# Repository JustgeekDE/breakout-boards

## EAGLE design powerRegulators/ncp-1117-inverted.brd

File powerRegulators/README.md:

# Power Regulators
Adapters to use the LM1117 SMD adjustable regulators on a breadboard.

The normal version has the same pinout as the common L78xx regulators, when looking at the components. The Inverted version has the L78xx footprint, when looking at the silkscreen side.

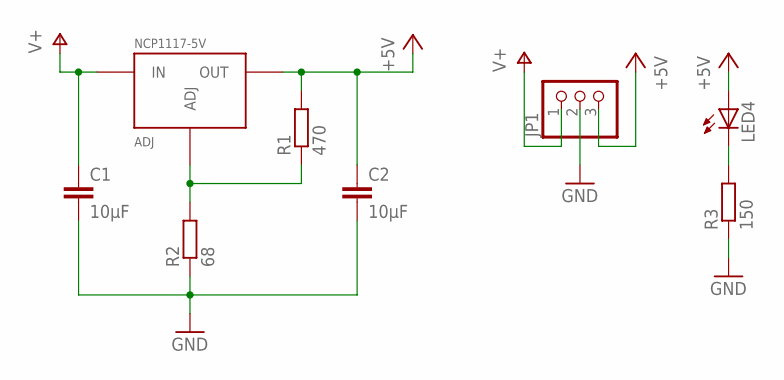
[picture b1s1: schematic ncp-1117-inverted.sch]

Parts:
C1, C2: 10µF; C0805
JP1: PINHD-1X3; 1X03
LED4: LEDCHIP-LED0603; CHIP-LED0603
NCP1117-5V: ADJ; TO252
R1: 470; R0603
R2: 68; R0603
R3: 150; R0603

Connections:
+5V: C2.1, JP1.3, LED4.A, NCP1117-5V.3 (OUT), R1.2
GND: C1.2, C2.2, JP1.2, R2.1, R3.1
unnamed: LED4.C, R3.2
unnamed: NCP1117-5V.1 (ADJ), R1.1, R2.2
V+: C1.1, JP1.1, NCP1117-5V.2 (IN)

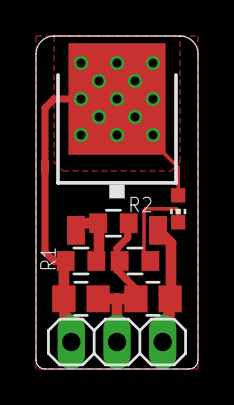
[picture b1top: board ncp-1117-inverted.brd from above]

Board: 2 copper layers, 9.0 x 18.5 mm, 9 parts (1 on the bottom side), 5 nets.

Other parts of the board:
U$1: LOGO-JUSTGEEK-XS

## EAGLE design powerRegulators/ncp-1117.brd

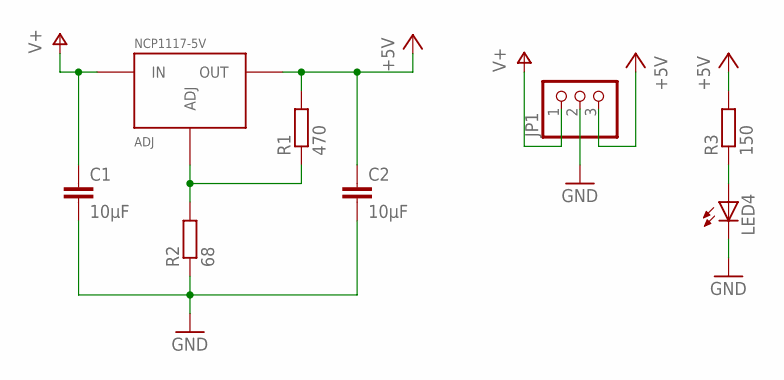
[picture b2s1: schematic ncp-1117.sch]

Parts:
C1, C2: 10µF; C0805
JP1: PINHD-1X3; 1X03
LED4: LEDCHIP-LED0603; CHIP-LED0603
NCP1117-5V: ADJ; TO252
R1: 470; R0603
R2: 68; R0603
R3: 150; R0603

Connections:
+5V: C2.1, JP1.3, NCP1117-5V.3 (OUT), R1.2, R3.2
GND: C1.2, C2.2, JP1.2, LED4.C, R2.1
unnamed: LED4.A, R3.1
unnamed: NCP1117-5V.1 (ADJ), R1.1, R2.2
V+: C1.1, JP1.1, NCP1117-5V.2 (IN)

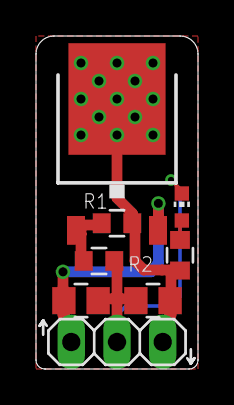
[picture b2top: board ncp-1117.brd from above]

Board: 2 copper layers, 9.0 x 18.5 mm, 9 parts (1 on the bottom side), 5 nets.

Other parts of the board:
U$1: LOGO-JUSTGEEK-XS

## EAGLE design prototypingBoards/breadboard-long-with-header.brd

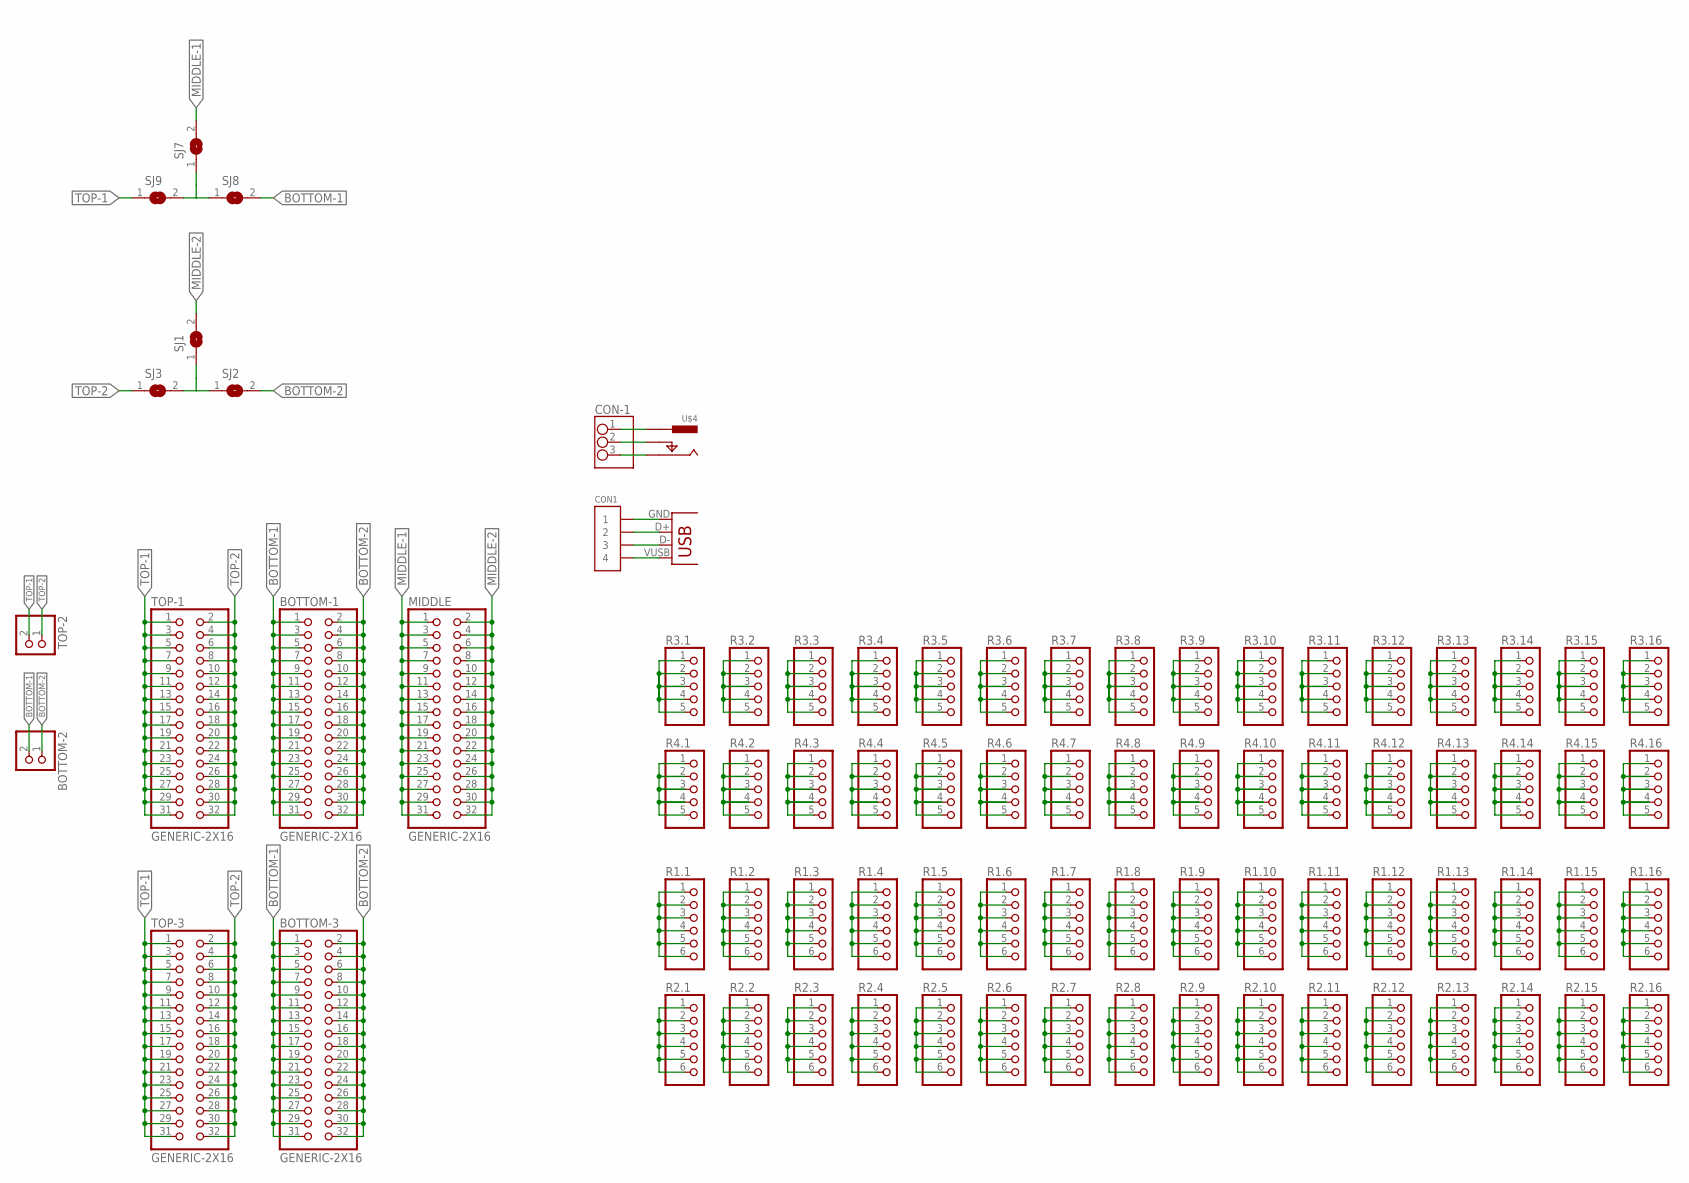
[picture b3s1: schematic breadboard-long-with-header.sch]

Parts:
BOTTOM-1, BOTTOM-3: GENERIC-2X16; PINHEADER-100MIL-2X16-NOSILK
BOTTOM-2: GENERIC-1X2; PINHEADER-100MIL-1X2-NOSILK
CON1: GENERIC-1X4STRAIGHT; PINHEADER-100MIL-1X4-NOSILK
CON-1: GENERIC-1X3; PINHEADER-100MIL-1X3-NOSILK
MIDDLE: GENERIC-2X16; PINHEADER-100MIL-2X16-NOSILK
R1.1, R1.2, R1.3, R1.4, R1.5, R1.6, R1.7, R1.8, R1.9, R1.10, R1.11, R1.12, R1.13, R1.14, R1.15, R1.16, R2.1, R2.2, R2.3, R2.4, R2.5, R2.6, R2.7, R2.8, R2.9, R2.10, R2.11, R2.12, R2.13, R2.14, R2.15, R2.16: GENERIC-1X6; PINHEADER-100MIL-1X6-NOSILK
R3.1, R3.2, R3.3, R3.4, R3.5, R3.6, R3.7, R3.8, R3.9, R3.10, R3.11, R3.12, R3.13, R3.14, R3.15, R3.16, R4.1, R4.2, R4.3, R4.4, R4.5, R4.6, R4.7, R4.8, R4.9, R4.10, R4.11, R4.12, R4.13, R4.14, R4.15, R4.16: GENERIC-1X5; PINHEADER-100MIL-1X5-NOSILK
SJ1, SJ2, SJ3, SJ7, SJ8, SJ9: SJ
TOP-1, TOP-3: GENERIC-2X16; PINHEADER-100MIL-2X16-NOSILK
TOP-2: GENERIC-1X2; PINHEADER-100MIL-1X2-NOSILK
U$3: USBMINI-HAND; USB-MINI-B-HAND_EXTRA_LONG
U$4: POWER-BARREL_JACKEBAY; POWER-BARREL-2MM1-EBAY

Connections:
BOTTOM-1: BOTTOM-1.1, BOTTOM-1.3, BOTTOM-1.5, BOTTOM-1.7, BOTTOM-1.9, BOTTOM-1.11, BOTTOM-1.13, BOTTOM-1.15, BOTTOM-1.17, BOTTOM-1.19, BOTTOM-1.21, BOTTOM-1.23, BOTTOM-1.25, BOTTOM-1.27, BOTTOM-1.29, BOTTOM-1.31, BOTTOM-2.2, BOTTOM-3.1, BOTTOM-3.3, BOTTOM-3.5, BOTTOM-3.7, BOTTOM-3.9, BOTTOM-3.11, BOTTOM-3.13, BOTTOM-3.15, BOTTOM-3.17, BOTTOM-3.19, BOTTOM-3.21, BOTTOM-3.23, BOTTOM-3.25, BOTTOM-3.27, BOTTOM-3.29, BOTTOM-3.31, SJ8.2
BOTTOM-2: BOTTOM-1.2, BOTTOM-1.4, BOTTOM-1.6, BOTTOM-1.8, BOTTOM-1.10, BOTTOM-1.12, BOTTOM-1.14, BOTTOM-1.16, BOTTOM-1.18, BOTTOM-1.20, BOTTOM-1.22, BOTTOM-1.24, BOTTOM-1.26, BOTTOM-1.28, BOTTOM-1.30, BOTTOM-1.32, BOTTOM-2.1, BOTTOM-3.2, BOTTOM-3.4, BOTTOM-3.6, BOTTOM-3.8, BOTTOM-3.10, BOTTOM-3.12, BOTTOM-3.14, BOTTOM-3.16, BOTTOM-3.18, BOTTOM-3.20, BOTTOM-3.22, BOTTOM-3.24, BOTTOM-3.26, BOTTOM-3.28, BOTTOM-3.30, BOTTOM-3.32, SJ2.2
CENTER: CON-1.1, U$4.P$4 (CENTER)
MIDDLE-1: MIDDLE.1, MIDDLE.3, MIDDLE.5, MIDDLE.7, MIDDLE.9, MIDDLE.11, MIDDLE.13, MIDDLE.15, MIDDLE.17, MIDDLE.19, MIDDLE.21, MIDDLE.23, MIDDLE.25, MIDDLE.27, MIDDLE.29, MIDDLE.31, SJ7.2
MIDDLE-2: MIDDLE.2, MIDDLE.4, MIDDLE.6, MIDDLE.8, MIDDLE.10, MIDDLE.12, MIDDLE.14, MIDDLE.16, MIDDLE.18, MIDDLE.20, MIDDLE.22, MIDDLE.24, MIDDLE.26, MIDDLE.28, MIDDLE.30, MIDDLE.32, SJ1.2
unnamed: R3.1.1, R3.1.2, R3.1.3, R3.1.4, R3.1.5
unnamed: R4.1.1, R4.1.2, R4.1.3, R4.1.4, R4.1.5
unnamed: R2.6.1, R2.6.2, R2.6.3, R2.6.4, R2.6.5, R2.6.6
unnamed: R1.6.1, R1.6.2, R1.6.3, R1.6.4, R1.6.5, R1.6.6
unnamed: R2.7.1, R2.7.2, R2.7.3, R2.7.4, R2.7.5, R2.7.6
unnamed: R1.7.1, R1.7.2, R1.7.3, R1.7.4, R1.7.5, R1.7.6
unnamed: R2.8.1, R2.8.2, R2.8.3, R2.8.4, R2.8.5, R2.8.6
unnamed: R1.8.1, R1.8.2, R1.8.3, R1.8.4, R1.8.5, R1.8.6
unnamed: R2.9.1, R2.9.2, R2.9.3, R2.9.4, R2.9.5, R2.9.6
unnamed: R2.1.1, R2.1.2, R2.1.3, R2.1.4, R2.1.5, R2.1.6
unnamed: R1.1.1, R1.1.2, R1.1.3, R1.1.4, R1.1.5, R1.1.6
unnamed: R2.3.1, R2.3.2, R2.3.3, R2.3.4, R2.3.5, R2.3.6
unnamed: R2.2.1, R2.2.2, R2.2.3, R2.2.4, R2.2.5, R2.2.6
unnamed: R1.2.1, R1.2.2, R1.2.3, R1.2.4, R1.2.5, R1.2.6
unnamed: R1.3.1, R1.3.2, R1.3.3, R1.3.4, R1.3.5, R1.3.6
unnamed: R2.4.1, R2.4.2, R2.4.3, R2.4.4, R2.4.5, R2.4.6
unnamed: R1.4.1, R1.4.2, R1.4.3, R1.4.4, R1.4.5, R1.4.6
unnamed: R2.5.1, R2.5.2, R2.5.3, R2.5.4, R2.5.5, R2.5.6
unnamed: R1.5.1, R1.5.2, R1.5.3, R1.5.4, R1.5.5, R1.5.6
unnamed: R3.2.1, R3.2.2, R3.2.3, R3.2.4, R3.2.5
unnamed: R4.2.1, R4.2.2, R4.2.3, R4.2.4, R4.2.5
unnamed: R3.3.1, R3.3.2, R3.3.3, R3.3.4, R3.3.5
unnamed: R4.3.1, R4.3.2, R4.3.3, R4.3.4, R4.3.5
unnamed: R3.4.1, R3.4.2, R3.4.3, R3.4.4, R3.4.5
unnamed: R4.4.1, R4.4.2, R4.4.3, R4.4.4, R4.4.5
unnamed: R3.5.1, R3.5.2, R3.5.3, R3.5.4, R3.5.5
unnamed: R4.5.1, R4.5.2, R4.5.3, R4.5.4, R4.5.5
unnamed: R3.6.1, R3.6.2, R3.6.3, R3.6.4, R3.6.5
unnamed: R4.6.1, R4.6.2, R4.6.3, R4.6.4, R4.6.5
unnamed: R3.7.1, R3.7.2, R3.7.3, R3.7.4, R3.7.5
unnamed: R4.7.1, R4.7.2, R4.7.3, R4.7.4, R4.7.5
unnamed: R3.8.1, R3.8.2, R3.8.3, R3.8.4, R3.8.5
unnamed: R4.8.1, R4.8.2, R4.8.3, R4.8.4, R4.8.5
unnamed: R3.9.1, R3.9.2, R3.9.3, R3.9.4, R3.9.5
unnamed: R4.9.1, R4.9.2, R4.9.3, R4.9.4, R4.9.5
unnamed: SJ1.1, SJ2.1, SJ3.2
unnamed: R1.9.1, R1.9.2, R1.9.3, R1.9.4, R1.9.5, R1.9.6
unnamed: SJ7.1, SJ8.1, SJ9.2
unnamed: R2.10.1, R2.10.2, R2.10.3, R2.10.4, R2.10.5, R2.10.6
unnamed: R1.10.1, R1.10.2, R1.10.3, R1.10.4, R1.10.5, R1.10.6
unnamed: R2.11.1, R2.11.2, R2.11.3, R2.11.4, R2.11.5, R2.11.6
unnamed: R1.11.1, R1.11.2, R1.11.3, R1.11.4, R1.11.5, R1.11.6
unnamed: R2.12.1, R2.12.2, R2.12.3, R2.12.4, R2.12.5, R2.12.6
unnamed: R1.12.1, R1.12.2, R1.12.3, R1.12.4, R1.12.5, R1.12.6
unnamed: R2.13.1, R2.13.2, R2.13.3, R2.13.4, R2.13.5, R2.13.6
unnamed: R1.13.1, R1.13.2, R1.13.3, R1.13.4, R1.13.5, R1.13.6
unnamed: R2.14.1, R2.14.2, R2.14.3, R2.14.4, R2.14.5, R2.14.6
unnamed: R1.14.1, R1.14.2, R1.14.3, R1.14.4, R1.14.5, R1.14.6
unnamed: R2.15.1, R2.15.2, R2.15.3, R2.15.4, R2.15.5, R2.15.6
unnamed: R1.15.1, R1.15.2, R1.15.3, R1.15.4, R1.15.5, R1.15.6
unnamed: R2.16.1, R2.16.2, R2.16.3, R2.16.4, R2.16.5, R2.16.6
unnamed: R1.16.1, R1.16.2, R1.16.3, R1.16.4, R1.16.5, R1.16.6
unnamed: R3.10.1, R3.10.2, R3.10.3, R3.10.4, R3.10.5
unnamed: R4.10.1, R4.10.2, R4.10.3, R4.10.4, R4.10.5
unnamed: R3.11.1, R3.11.2, R3.11.3, R3.11.4, R3.11.5
unnamed: R4.11.1, R4.11.2, R4.11.3, R4.11.4, R4.11.5
unnamed: R3.12.1, R3.12.2, R3.12.3, R3.12.4, R3.12.5
unnamed: R4.12.1, R4.12.2, R4.12.3, R4.12.4, R4.12.5
unnamed: R3.13.1, R3.13.2, R3.13.3, R3.13.4, R3.13.5
unnamed: R4.13.1, R4.13.2, R4.13.3, R4.13.4, R4.13.5
unnamed: R3.14.1, R3.14.2, R3.14.3, R3.14.4, R3.14.5
unnamed: R4.14.1, R4.14.2, R4.14.3, R4.14.4, R4.14.5
unnamed: R3.15.1, R3.15.2, R3.15.3, R3.15.4, R3.15.5
unnamed: R4.15.1, R4.15.2, R4.15.3, R4.15.4, R4.15.5
unnamed: R3.16.1, R3.16.2, R3.16.3, R3.16.4, R3.16.5
unnamed: R4.16.1, R4.16.2, R4.16.3, R4.16.4, R4.16.5
SLEEVE: CON-1.3, U$4.P$3 (OUTER)
SWITCH: CON-1.2, U$4.P$2 (SWITCH)
TOP-1: SJ9.1, TOP-1.1, TOP-1.3, TOP-1.5, TOP-1.7, TOP-1.9, TOP-1.11, TOP-1.13, TOP-1.15, TOP-1.17, TOP-1.19, TOP-1.21, TOP-1.23, TOP-1.25, TOP-1.27, TOP-1.29, TOP-1.31, TOP-2.2, TOP-3.1, TOP-3.3, TOP-3.5, TOP-3.7, TOP-3.9, TOP-3.11, TOP-3.13, TOP-3.15, TOP-3.17, TOP-3.19, TOP-3.21, TOP-3.23, TOP-3.25, TOP-3.27, TOP-3.29, TOP-3.31
TOP-2: SJ3.1, TOP-1.2, TOP-1.4, TOP-1.6, TOP-1.8, TOP-1.10, TOP-1.12, TOP-1.14, TOP-1.16, TOP-1.18, TOP-1.20, TOP-1.22, TOP-1.24, TOP-1.26, TOP-1.28, TOP-1.30, TOP-1.32, TOP-2.1, TOP-3.2, TOP-3.4, TOP-3.6, TOP-3.8, TOP-3.10, TOP-3.12, TOP-3.14, TOP-3.16, TOP-3.18, TOP-3.20, TOP-3.22, TOP-3.24, TOP-3.26, TOP-3.28, TOP-3.30, TOP-3.32
USB-D+: CON1.2, U$3.D+
USB-DI: CON1.3, U$3.D-
USB-GND: CON1.1, U$3.GND
USB-V+: CON1.4, U$3.VUSB (VBUS)

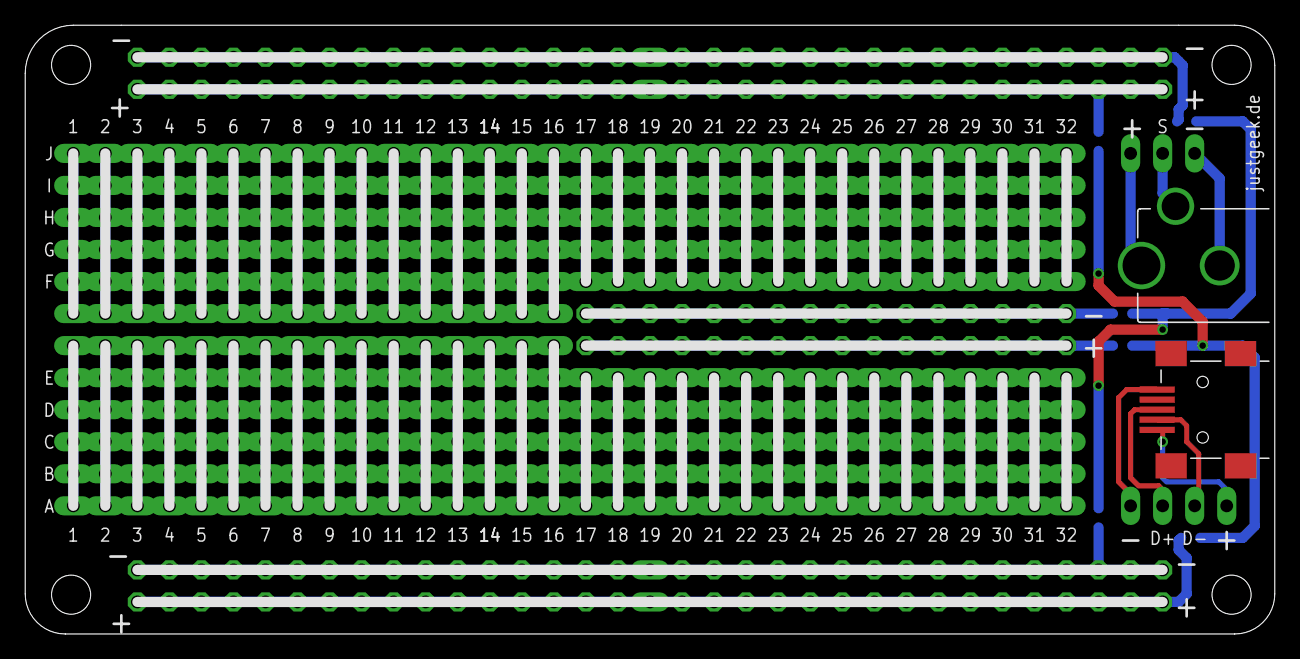
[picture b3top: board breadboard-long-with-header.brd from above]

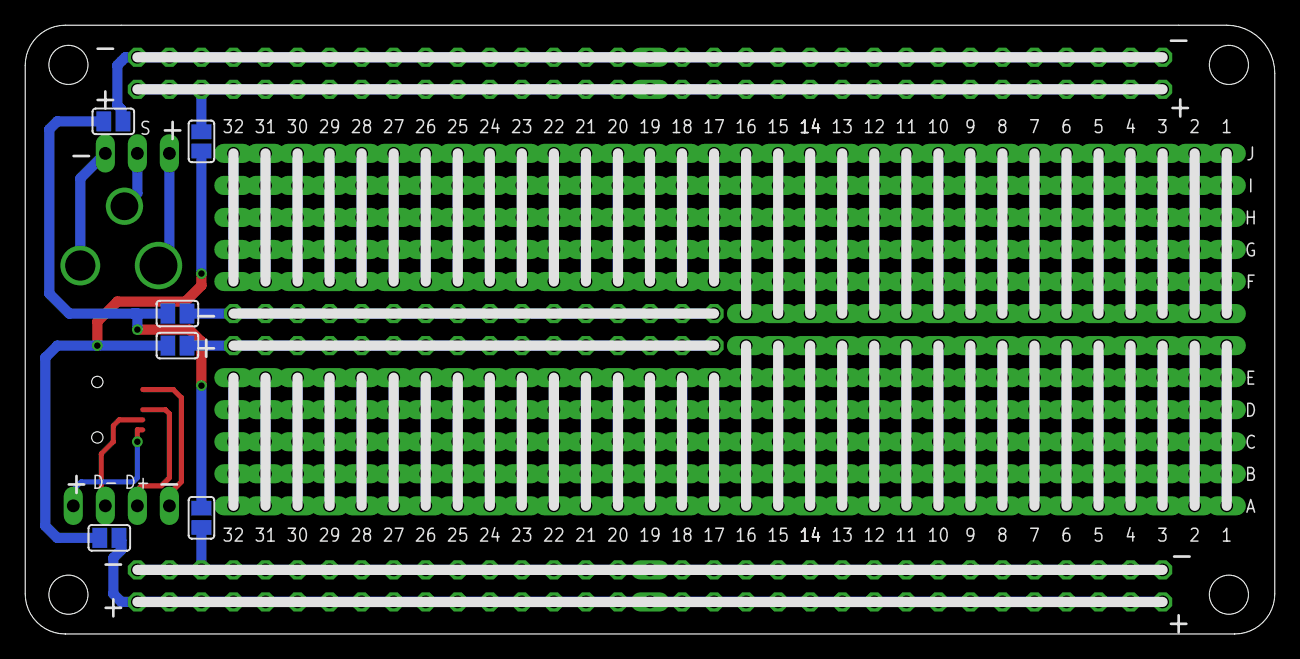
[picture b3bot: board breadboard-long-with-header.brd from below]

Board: 2 copper layers, 99.1 x 48.3 mm, 81 parts (6 on the bottom side), 79 nets.

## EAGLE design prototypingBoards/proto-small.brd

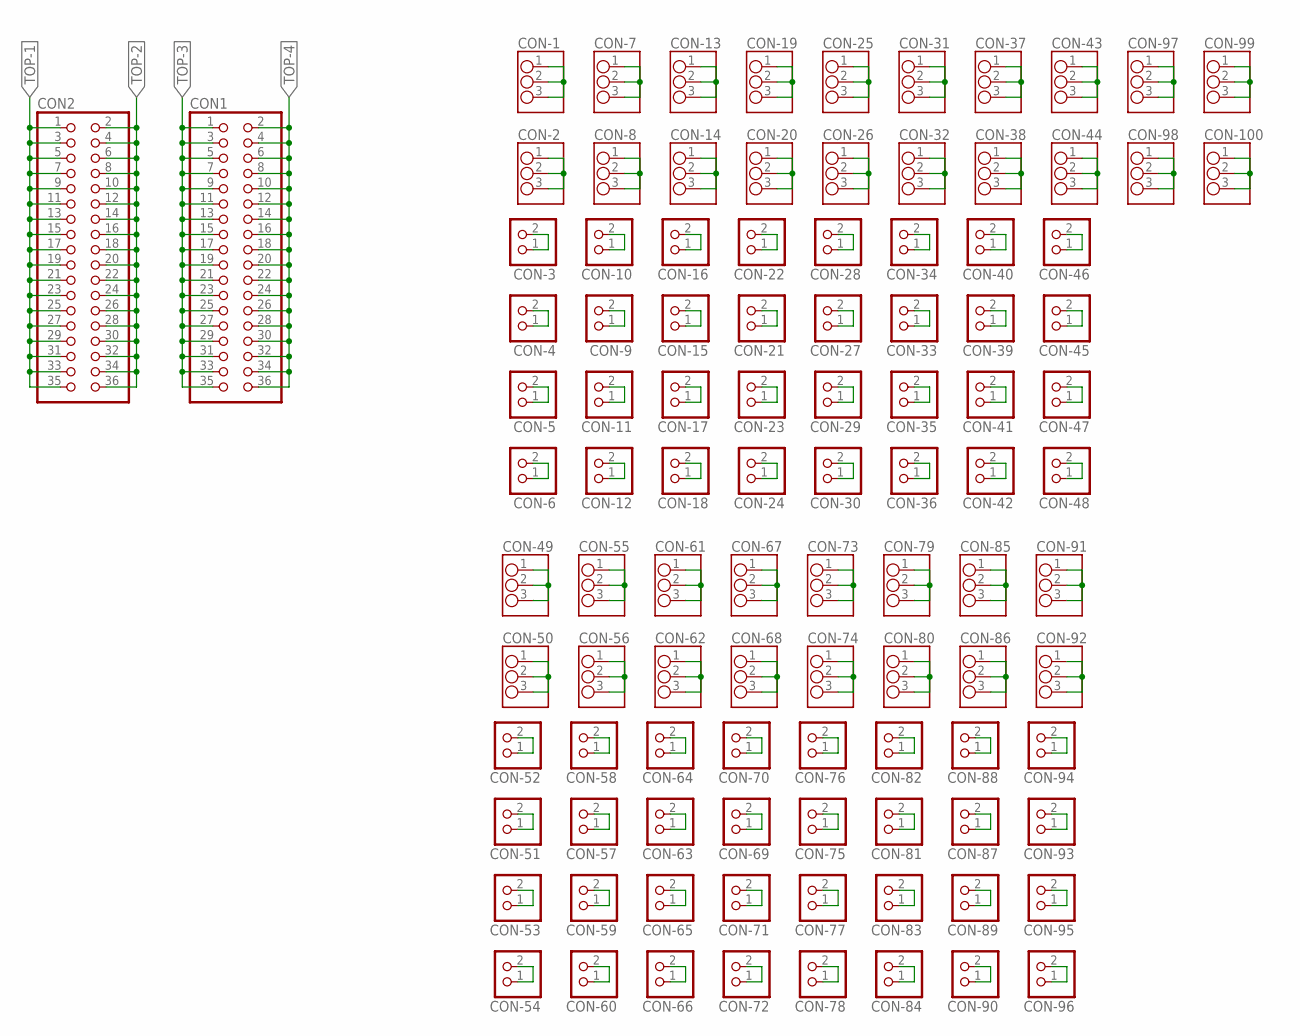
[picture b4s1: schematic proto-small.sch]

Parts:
CON1, CON2: GENERIC-2X18; PINHEADER-100MIL-2X18-NOSILK
CON-1, CON-2, CON-7, CON-8, CON-13, CON-14, CON-19, CON-20, CON-25, CON-26, CON-31, CON-32, CON-37, CON-38, CON-43, CON-44, CON-49, CON-50, CON-55, CON-56, CON-61, CON-62, CON-67, CON-68, CON-73, CON-74, CON-79, CON-80, CON-85, CON-86, CON-91, CON-92, CON-97, CON-98, CON-99, CON-100: GENERIC-1X3; PINHEADER-100MIL-1X3-NOSILK
CON-3, CON-4, CON-5, CON-6, CON-9, CON-10, CON-11, CON-12, CON-15, CON-16, CON-17, CON-18, CON-21, CON-22, CON-23, CON-24, CON-27, CON-28, CON-29, CON-30, CON-33, CON-34, CON-35, CON-36, CON-39, CON-40, CON-41, CON-42, CON-45, CON-46, CON-47, CON-48, CON-51, CON-52, CON-53, CON-54, CON-57, CON-58, CON-59, CON-60, CON-63, CON-64, CON-65, CON-66, CON-69, CON-70, CON-71, CON-72, CON-75, CON-76, CON-77, CON-78, CON-81, CON-82, CON-83, CON-84, CON-87, CON-88, CON-89, CON-90, CON-93, CON-94, CON-95, CON-96: GENERIC-1X2; PINHEADER-100MIL-1X2-NOSILK

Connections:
unnamed: CON-1.1, CON-1.2, CON-1.3
unnamed: CON-2.1, CON-2.2, CON-2.3
unnamed: CON-3.1, CON-3.2
unnamed: CON-7.1, CON-7.2, CON-7.3
unnamed: CON-5.1, CON-5.2
unnamed: CON-6.1, CON-6.2
unnamed: CON-8.1, CON-8.2, CON-8.3
unnamed: CON-10.1, CON-10.2
unnamed: CON-11.1, CON-11.2
unnamed: CON-12.1, CON-12.2
unnamed: CON-13.1, CON-13.2, CON-13.3
unnamed: CON-14.1, CON-14.2, CON-14.3
unnamed: CON-16.1, CON-16.2
unnamed: CON-17.1, CON-17.2
unnamed: CON-18.1, CON-18.2
unnamed: CON-19.1, CON-19.2, CON-19.3
unnamed: CON-20.1, CON-20.2, CON-20.3
unnamed: CON-22.1, CON-22.2
unnamed: CON-23.1, CON-23.2
unnamed: CON-24.1, CON-24.2
unnamed: CON-25.1, CON-25.2, CON-25.3
unnamed: CON-26.1, CON-26.2, CON-26.3
unnamed: CON-28.1, CON-28.2
unnamed: CON-29.1, CON-29.2
unnamed: CON-30.1, CON-30.2
unnamed: CON-31.1, CON-31.2, CON-31.3
unnamed: CON-32.1, CON-32.2, CON-32.3
unnamed: CON-34.1, CON-34.2
unnamed: CON-35.1, CON-35.2
unnamed: CON-36.1, CON-36.2
unnamed: CON-37.1, CON-37.2, CON-37.3
unnamed: CON-38.1, CON-38.2, CON-38.3
unnamed: CON-40.1, CON-40.2
unnamed: CON-41.1, CON-41.2
unnamed: CON-42.1, CON-42.2
unnamed: CON-43.1, CON-43.2, CON-43.3
unnamed: CON-44.1, CON-44.2, CON-44.3
unnamed: CON-46.1, CON-46.2
unnamed: CON-47.1, CON-47.2
unnamed: CON-48.1, CON-48.2
unnamed: CON-49.1, CON-49.2, CON-49.3
unnamed: CON-50.1, CON-50.2, CON-50.3
unnamed: CON-52.1, CON-52.2
unnamed: CON-53.1, CON-53.2
unnamed: CON-54.1, CON-54.2
unnamed: CON-55.1, CON-55.2, CON-55.3
unnamed: CON-56.1, CON-56.2, CON-56.3
unnamed: CON-58.1, CON-58.2
unnamed: CON-59.1, CON-59.2
unnamed: CON-60.1, CON-60.2
unnamed: CON-61.1, CON-61.2, CON-61.3
unnamed: CON-62.1, CON-62.2, CON-62.3
unnamed: CON-64.1, CON-64.2
unnamed: CON-65.1, CON-65.2
unnamed: CON-66.1, CON-66.2
unnamed: CON-67.1, CON-67.2, CON-67.3
unnamed: CON-68.1, CON-68.2, CON-68.3
unnamed: CON-70.1, CON-70.2
unnamed: CON-71.1, CON-71.2
unnamed: CON-72.1, CON-72.2
unnamed: CON-73.1, CON-73.2, CON-73.3
unnamed: CON-74.1, CON-74.2, CON-74.3
unnamed: CON-76.1, CON-76.2
unnamed: CON-77.1, CON-77.2
unnamed: CON-78.1, CON-78.2
unnamed: CON-79.1, CON-79.2, CON-79.3
unnamed: CON-80.1, CON-80.2, CON-80.3
unnamed: CON-82.1, CON-82.2
unnamed: CON-83.1, CON-83.2
unnamed: CON-84.1, CON-84.2
unnamed: CON-85.1, CON-85.2, CON-85.3
unnamed: CON-86.1, CON-86.2, CON-86.3
unnamed: CON-88.1, CON-88.2
unnamed: CON-89.1, CON-89.2
unnamed: CON-90.1, CON-90.2
unnamed: CON-91.1, CON-91.2, CON-91.3
unnamed: CON-92.1, CON-92.2, CON-92.3
unnamed: CON-94.1, CON-94.2
unnamed: CON-95.1, CON-95.2
unnamed: CON-96.1, CON-96.2
unnamed: CON-97.1, CON-97.2, CON-97.3
unnamed: CON-98.1, CON-98.2, CON-98.3
unnamed: CON-99.1, CON-99.2, CON-99.3
unnamed: CON-100.1, CON-100.2, CON-100.3
N$-1: CON-9.1, CON-9.2
N$-2: CON-15.1, CON-15.2
N$-3: CON-21.1, CON-21.2
N$-4: CON-4.1, CON-4.2
N$-5: CON-27.1, CON-27.2
N$-6: CON-33.1, CON-33.2
N$-7: CON-39.1, CON-39.2
N$-8: CON-45.1, CON-45.2
N$-9: CON-51.1, CON-51.2
N$-10: CON-57.1, CON-57.2
N$-11: CON-63.1, CON-63.2
N$-12: CON-69.1, CON-69.2
N$-13: CON-75.1, CON-75.2
N$-14: CON-81.1, CON-81.2
N$-15: CON-87.1, CON-87.2
N$-16: CON-93.1, CON-93.2
TOP-1: CON2.1, CON2.3, CON2.5, CON2.7, CON2.9, CON2.11, CON2.13, CON2.15, CON2.17, CON2.19, CON2.21, CON2.23, CON2.25, CON2.27, CON2.29, CON2.31, CON2.33, CON2.35
TOP-2: CON2.2, CON2.4, CON2.6, CON2.8, CON2.10, CON2.12, CON2.14, CON2.16, CON2.18, CON2.20, CON2.22, CON2.24, CON2.26, CON2.28, CON2.30, CON2.32, CON2.34, CON2.36
TOP-3: CON1.1, CON1.3, CON1.5, CON1.7, CON1.9, CON1.11, CON1.13, CON1.15, CON1.17, CON1.19, CON1.21, CON1.23, CON1.25, CON1.27, CON1.29, CON1.31, CON1.33, CON1.35
TOP-4: CON1.2, CON1.4, CON1.6, CON1.8, CON1.10, CON1.12, CON1.14, CON1.16, CON1.18, CON1.20, CON1.22, CON1.24, CON1.26, CON1.28, CON1.30, CON1.32, CON1.34, CON1.36

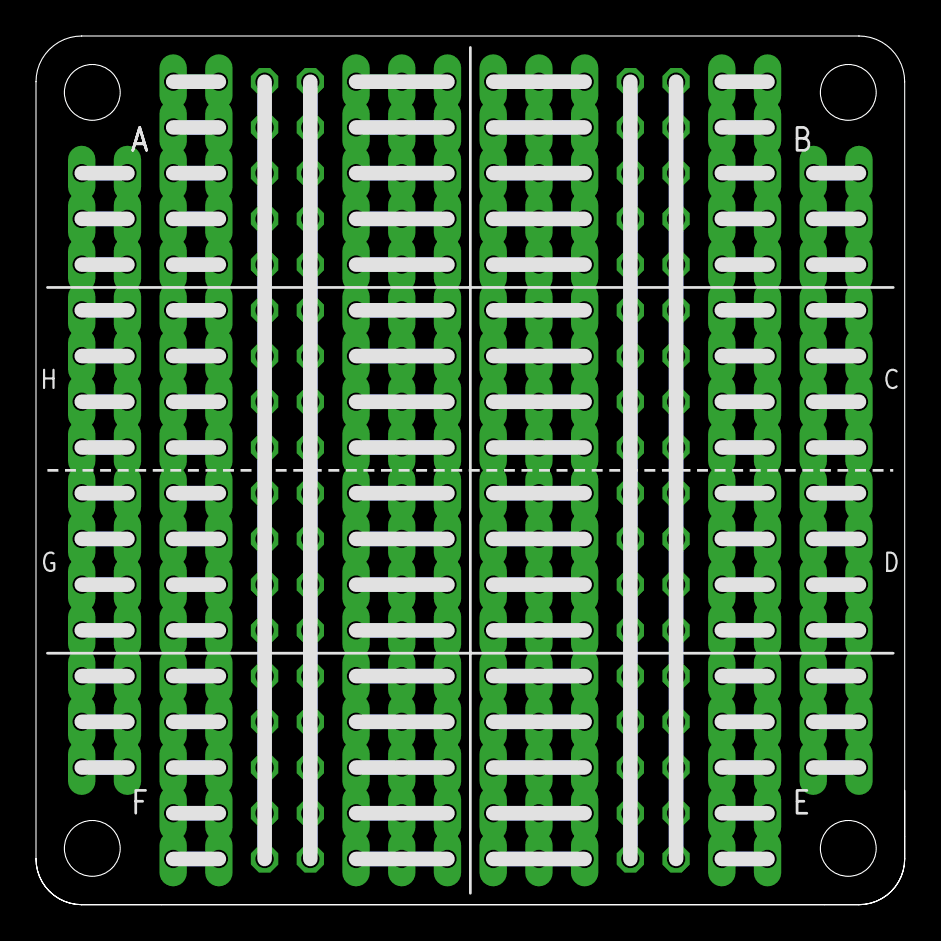
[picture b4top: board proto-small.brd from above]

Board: 2 copper layers, 48.3 x 48.3 mm, 103 parts (0 on the bottom side), 104 nets.

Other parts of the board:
U$1: OUTLINE-SOB-5X5-IMPERIAL
